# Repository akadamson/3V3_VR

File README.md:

3V3_VR
======

Simple 3v3 Voltage regulator with RC 3 pin headers on both sides.

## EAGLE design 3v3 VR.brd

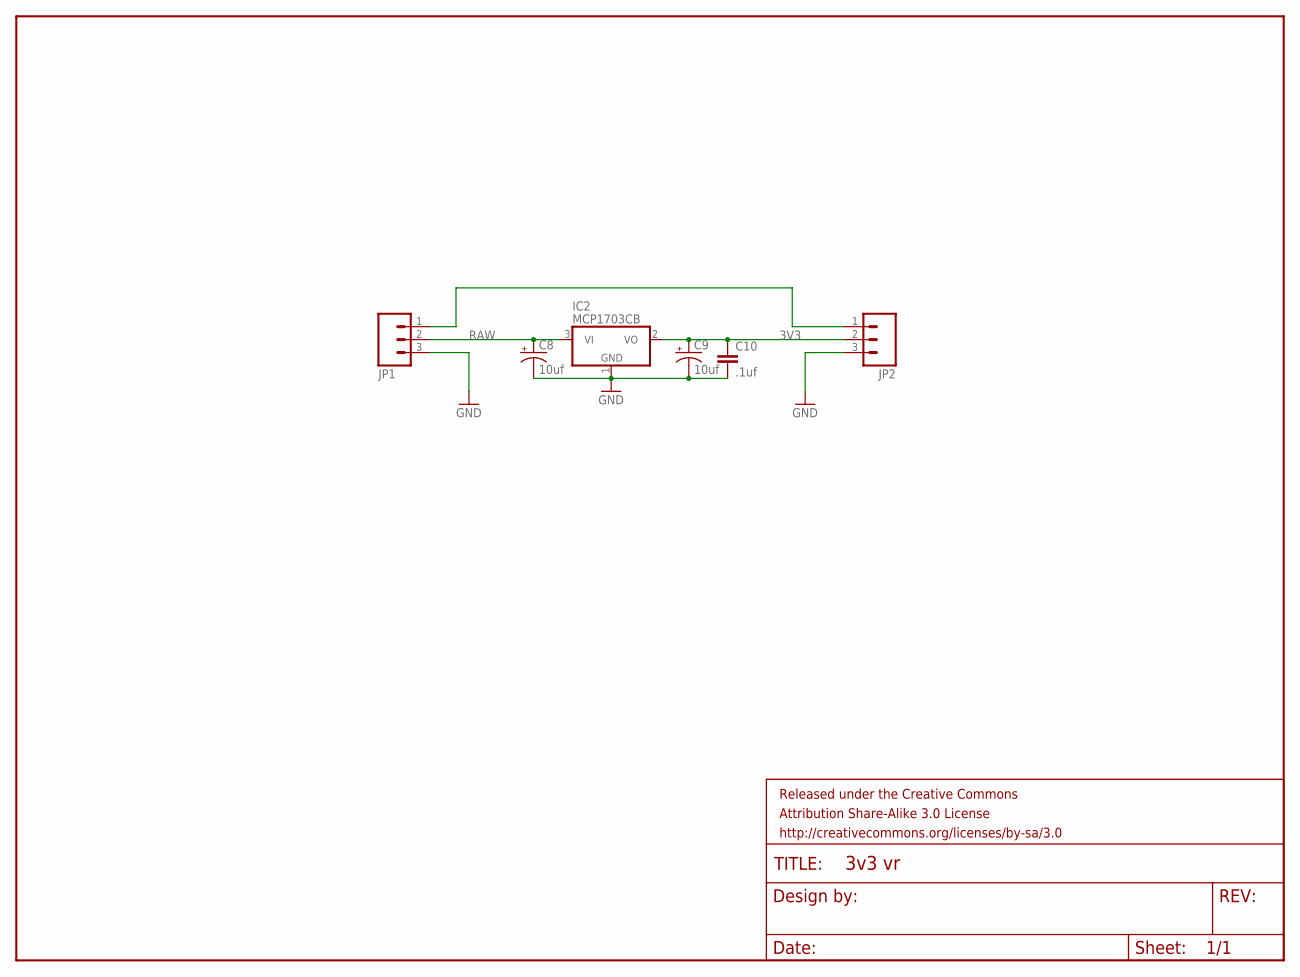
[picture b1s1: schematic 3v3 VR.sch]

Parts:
C8, C9: 10uf; EIA3216
C10: .1uf; 0402-CAP
FRAME1: FRAME-LETTER; CREATIVE_COMMONS
IC2: MCP1703CB; SOT23
JP1, JP2: M031X03_NO_SILK; 1X03_NO_SILK

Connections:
3V3: C9.A (+), C10.1, IC2.2 (VO), JP2.2
GND: C8.C (-), C9.C (-), C10.2, IC2.1 (GND), JP1.3, JP2.3
unnamed: JP1.1, JP2.1
RAW: C8.A (+), IC2.3 (VI), JP1.2

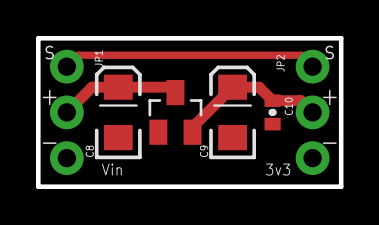
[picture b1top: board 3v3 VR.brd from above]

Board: 2 copper layers, 16.8 x 8.2 mm, 7 parts (0 on the bottom side), 4 nets.

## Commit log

2013-10-18 added pdf file of design

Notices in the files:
parts and their libraries:
SparkFun-Connectors: Licensing: CC v3.0 Share-Alike You are welcome to use this library for commercial purposes.
SparkFun-Aesthetics: Released under the Creative Commons Attribution Share-Alike 3.0 License
SparkFun-Aesthetics: http://creativecommons.org/licenses/by-sa/3.0
